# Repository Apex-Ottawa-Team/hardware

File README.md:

# Apex Hardware

## Overview

This repository contains the hardware design files for Ottawa Skybound's weather ballon for [Apex](https://apex.hackclub.com). The repository contains of multiple PCB modules designed in KiCad. The system includes a motherboard, wireless communication module, and various sensor interfaces.

## Boards

LoRa Module: Wireless communication module using LoRa technology. Designed by Adam Turaj

Motherboard: Main control board for the Apex system. Designed by Adam Turaj

Sensor Board: A board containing an IMU and temperature reader. Designed by Joshua Gallinger

Strain ADC: Analog-to-digital converter board for strain measurements. Designed by Adam Turaj

Archive/RF Module: Previous design iteration of the LoRa board. Designed by Adam Turaj

Gas Sensor: Collects data on TVOC concentrations in the air. Designed by Aryan Zafer

Ground RF: Board used to communicate and receive data from the weather balloon. Designed by Aryan Zafer

## Development Requirements

KiCad 9.0 or newer

## License

This project is licensed under the GNU GENERAL PUBLIC LICENSE. The license can be found [here](https://github.com/Apex-Ottawa-Team/hardware/blob/main/LICENSE).

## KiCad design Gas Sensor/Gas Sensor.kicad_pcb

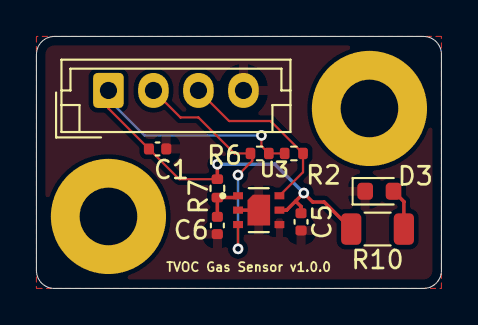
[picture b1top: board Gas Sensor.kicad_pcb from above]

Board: 2 copper layers, 22.5 x 14.0 mm, 10 parts (0 on the bottom side), 6 nets.

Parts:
C1: 10uF; C_0402_1005Metric
C5, C6: 0.1uF; C_0402_1005Metric
D3: LED; LED_0603_1608Metric
J1: Conn_Sensors; JST_EH_B4B-EH-A_1x04_P2.50mm_Vertical
R2, R6: 10k; R_0402_1005Metric
R7: 4.7; R_0402_1005Metric
R10: 220; R_1206_3216Metric
U3: SGP40-D-R4; XCDR_SGP40-D-R4

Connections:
+3.3V: C1.1, C5.1, J1.1 (VCC), R2.1, R6.2, R7.2, R10.1, U3.5 (VDDH)
GND: C1.2, C5.2, C6.2, D3.1 (K), J1.4 (GND), U3.2 (VSS), U3.4 (N/A), U3.7 (EXP)
unnamed: D3.2 (A), R10.2
unnamed: C6.1, R7.1, U3.1 (VDD)
SCL: J1.3 (SNS_SCL), R2.2, U3.6 (SCL)
SDA: J1.2 (SNS_SDA), R6.1, U3.3 (SDA)

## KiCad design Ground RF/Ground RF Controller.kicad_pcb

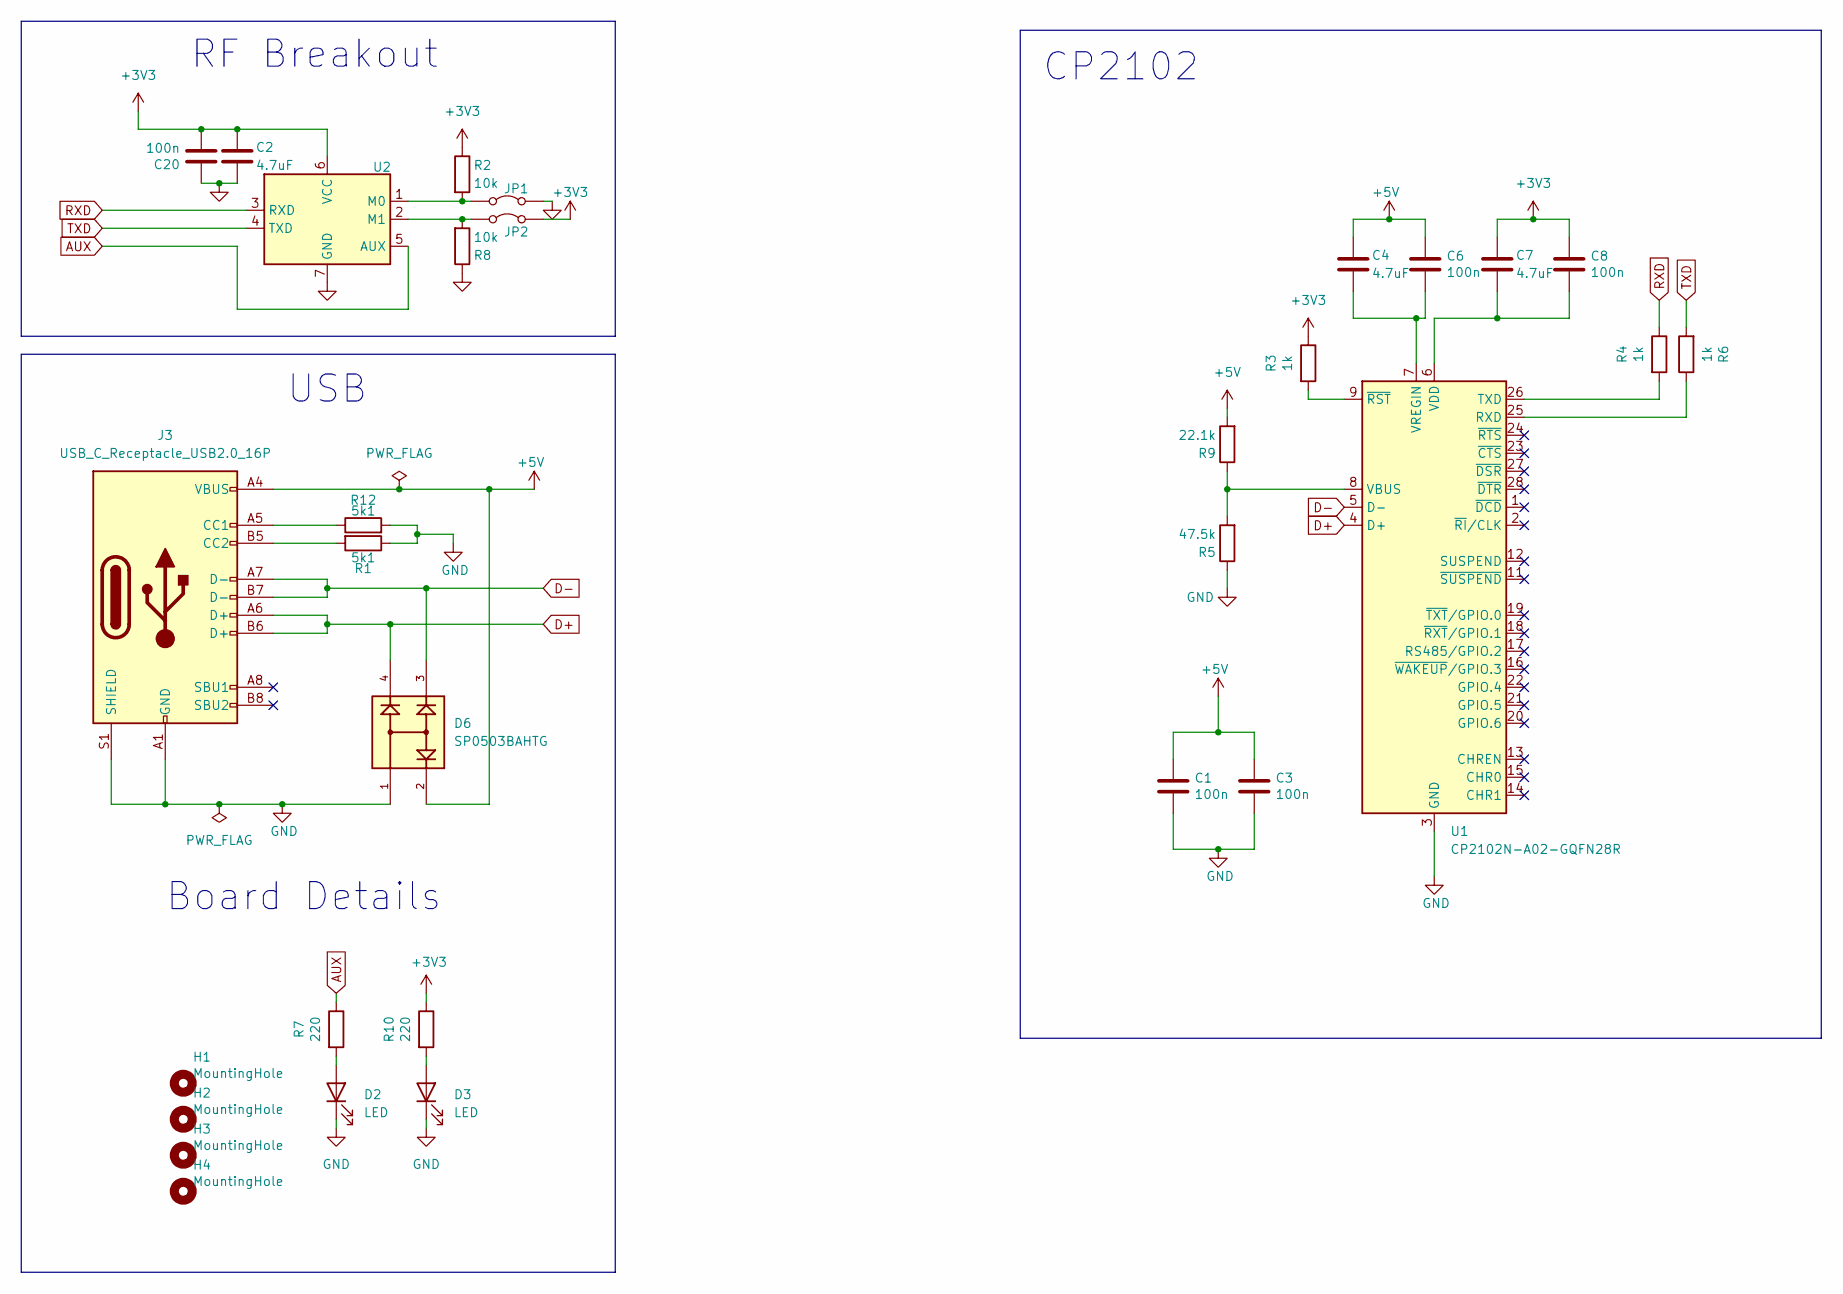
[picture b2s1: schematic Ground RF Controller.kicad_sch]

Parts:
C1, C3, C6, C8, C20: 100n; C_0402_1005Metric; MPN GRM152R61A104KE19D
C2, C4, C7: 4.7uF; C_0402_1005Metric; MPN GRM155R60J475ME47D
D2, D3: LED; LED_0603_1608Metric; MPN RC0603FR-075K1L
D6: SP0503BAHTG; SOT143; PARTREV N/A
H1, H2, H3, H4: MountingHole; MountingHole_2.7mm_M2.5
J3: USB_C_Receptacle_USB2.0_16P; USB_C_Receptacle_GCT_USB4105-xx-A_16P_TopMnt_Horizontal; MPN USB4105-GF-A-120
JP1, JP2: Jumper_2_Bridged; SolderJumper-2_P1.3mm_Open_RoundedPad1.0x1.5mm
R1, R12: 5k1; R_0603_1608Metric; MPN RC0603FR-075K1L
R2, R8: 10k; R_0402_1005Metric; MPN RC0402JR-0710KL
R3, R4, R6: 1k; R_0805_2012Metric; MPN RC0805JR-071KL
R5: 47.5k; R_0402_1005Metric; MPN CRCW040247K5FKEDC
R7, R10: 220; R_1206_3216Metric; MPN RC1206JR-10220RL
R9: 22.1k; R_0402_1005Metric; MPN CRCW040222K1FKEDC
U1: CP2102N-A02-GQFN28R; QFN-28-1EP_5x5mm_P0.5mm_EP3.35x3.35mm; MPN CP2102N-A02-GQFN28R
U2: EBYTE-E220-900T22D

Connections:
+3V3: C2.1, C7.1, C8.1, C20.2, JP2.2 (B), R2.1, R3.1, R10.1, U2.6 (VCC)
+5V: C1.1, C3.1, C4.1, C6.1, D6.2, J3.A4 (VBUS), J3.A9 (VBUS), J3.B4 (VBUS), J3.B9 (VBUS), R9.2
AUX: R7.1, U2.5 (AUX)
D+: D6.4, J3.A6 (D+), J3.B6 (D+), U1.4 (D+)
D-: D6.3, J3.A7 (D-), J3.B7 (D-), U1.5 (D-)
GND: C1.2, C2.2, C3.2, C20.1, D2.1 (K), D3.1 (K), D6.1, J3.A1 (GND), J3.A12 (GND), J3.B1 (GND), J3.B12 (GND), J3.S1 (SHIELD), JP1.2 (B), R1.1, R5.1, R8.1, R12.2, U1.3 (GND), U1.29 (GND), U2.7 (GND)
unnamed: D2.2 (A), R7.2
unnamed: D3.2 (A), R10.2
unnamed: J3.A5 (CC1), R12.1
unnamed: J3.B5 (CC2), R1.2
unnamed: JP1.1 (A), R2.2, U2.1 (M0)
unnamed: JP2.1 (A), R8.2, U2.2 (M1)
unnamed: R6.1, U1.25 (RXD)
unnamed: R4.2, U1.26 (TXD)
unnamed: R5.2, R9.1, U1.8 (VBUS)
unnamed: C7.2, C8.2, U1.6 (VDD)
unnamed: C4.2, C6.2, U1.7 (VREGIN)
unnamed: R3.2, U1.9 (~RST)
RXD: R4.1, U2.3 (RXD)
TXD: R6.2, U2.4 (TXD)

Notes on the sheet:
USB
CP2102
RF Breakout
Board Details

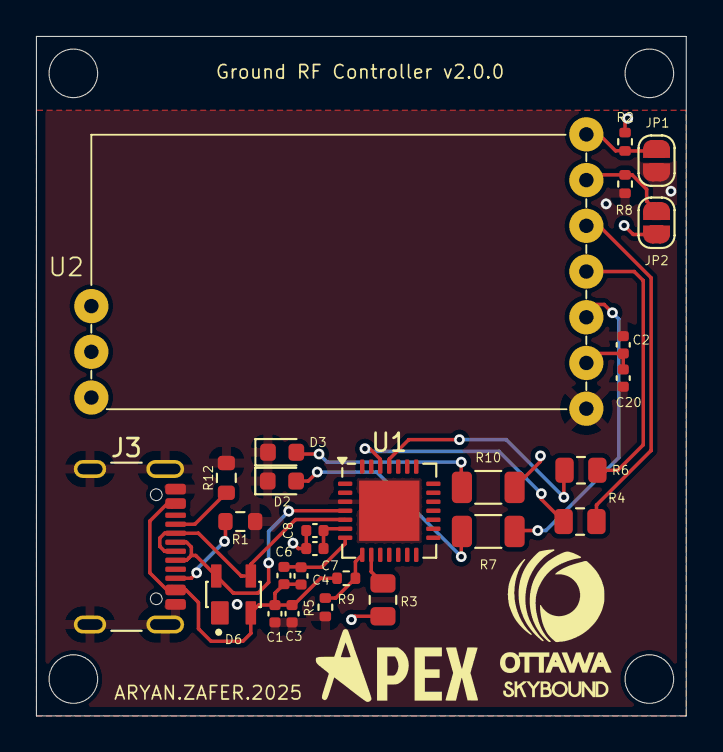
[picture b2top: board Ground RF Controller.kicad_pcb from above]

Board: 4 copper layers, 36.1 x 37.8 mm, 31 parts (0 on the bottom side), 20 nets.

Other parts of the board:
H3#2, H3#3, H3#4: MountingHole; MountingHole_2.7mm_M2.5

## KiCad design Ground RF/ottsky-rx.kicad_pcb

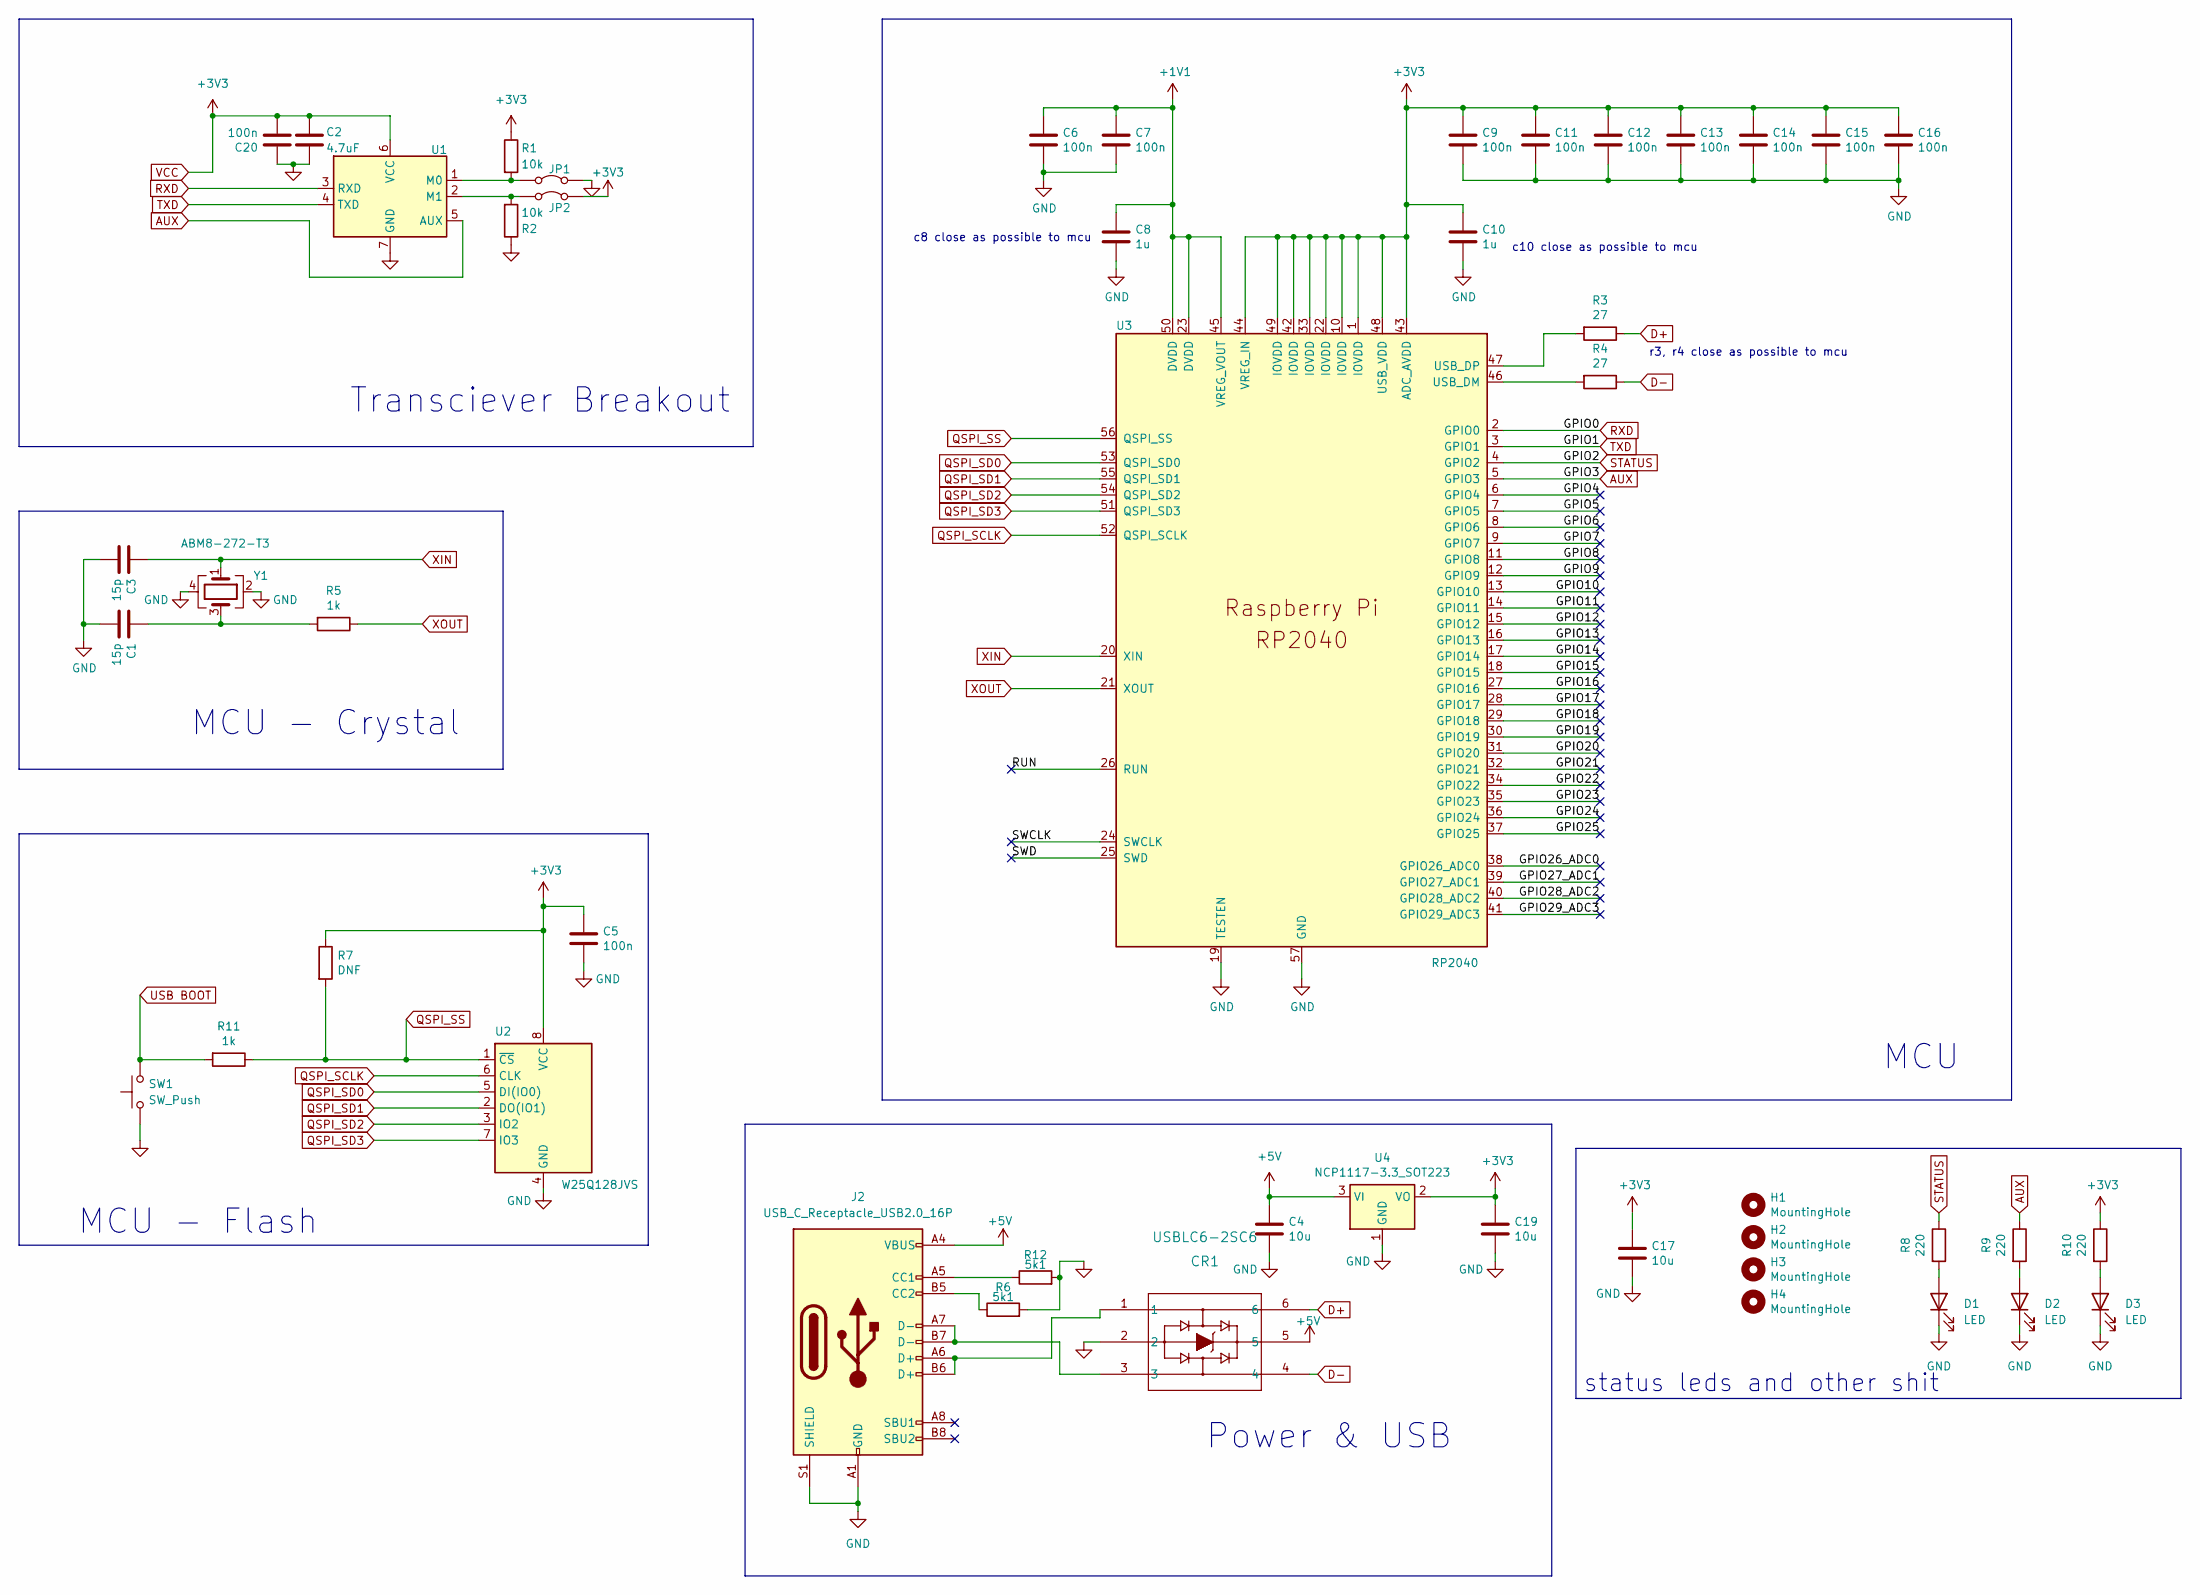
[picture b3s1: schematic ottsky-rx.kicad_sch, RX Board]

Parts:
C1, C3: 15p; C_0402_1005Metric; MPN GCQ1555C1H150JB01D
C2: 4.7uF; C_0402_1005Metric; MPN GRM155R60J475ME47D
C4, C17, C19: 10u; C_1210_3225Metric; MPN GMC32X5R106K50NT
C5, C6, C7, C9, C11, C12, C13, C14, C15, C16, C20: 100n; C_0402_1005Metric; MPN GRM152R61A104KE19D
C8: 1u; C_0402_1005Metric; MPN GRM152R60J105ME15D
C10: 1u; C_1206_3216Metric; MPN GRM31CR71E105KA01L
CR1: USBLC6-2SC6; SOT23-6L_STM; MPN USBLC6-2SC6
D1, D2, D3: LED; LED_0603_1608Metric; MPN RC0603FR-075K1L
H1, H2, H3, H4: MountingHole; MountingHole_2.7mm_M2.5
J2: USB_C_Receptacle_USB2.0_16P; USB_C_Receptacle_GCT_USB4105-xx-A_16P_TopMnt_Horizontal; MPN USB4105-GF-A-120
JP1, JP2: Jumper_2_Bridged; SolderJumper-2_P1.3mm_Open_RoundedPad1.0x1.5mm
R1, R2: 10k; R_0402_1005Metric; MPN RC0402JR-0710KL
R3, R4: 27; R_0402_1005Metric; MPN RC0402FR-7W27RL
R5, R11: 1k; R_0805_2012Metric; MPN RC0805JR-071KL
R6, R12: 5k1; R_0603_1608Metric; MPN RC0603FR-075K1L
R7: DNF; R_1206_3216Metric; MPN RC1206FR-130RL
R8, R9, R10: 220; R_1206_3216Metric; MPN RC1206JR-10220RL
SW1: SW_Push; SW_SPST_B3U-1000P; MPN B3U-1000P
U1: EBYTE-E220-900T22D
U2: W25Q128JVS; SOIC-8_5.23x5.23mm_P1.27mm; MPN W25Q128JVSIM TR
U3: RP2040; RP2040-QFN-56; MPN SC0914(13)
U4: NCP1117-3.3_SOT223; SOT-223-3_TabPin2; MPN NCP1117LPST33T3G
Y1: ABM8-272-T3; Crystal_SMD_3225-4Pin_3.2x2.5mm; MPN ABM8-272-T3

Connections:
+1V1: C6.1, C7.1, C8.1, U3.23 (DVDD), U3.45 (VREG_VOUT), U3.50 (DVDD)
+5V: C4.1, CR1.5, J2.A4 (VBUS), J2.A9 (VBUS), J2.B4 (VBUS), J2.B9 (VBUS), U4.3 (VI)
/GPIO4: U3.6 (GPIO4)
/GPIO5: U3.7 (GPIO5)
/GPIO6: U3.8 (GPIO6)
/GPIO7: U3.9 (GPIO7)
/GPIO8: U3.11 (GPIO8)
/GPIO9: U3.12 (GPIO9)
/GPIO10: U3.13 (GPIO10)
/GPIO11: U3.14 (GPIO11)
/GPIO12: U3.15 (GPIO12)
/GPIO13: U3.16 (GPIO13)
/GPIO14: U3.17 (GPIO14)
/GPIO15: U3.18 (GPIO15)
/GPIO16: U3.27 (GPIO16)
/GPIO17: U3.28 (GPIO17)
/GPIO18: U3.29 (GPIO18)
/GPIO19: U3.30 (GPIO19)
/GPIO20: U3.31 (GPIO20)
/GPIO21: U3.32 (GPIO21)
/GPIO22: U3.34 (GPIO22)
/GPIO23: U3.35 (GPIO23)
/GPIO24: U3.36 (GPIO24)
/GPIO25: U3.37 (GPIO25)
/GPIO26_ADC0: U3.38 (GPIO26_ADC0)
/GPIO27_ADC1: U3.39 (GPIO27_ADC1)
/GPIO28_ADC2: U3.40 (GPIO28_ADC2)
/GPIO29_ADC3: U3.41 (GPIO29_ADC3)
/RUN: U3.26 (RUN)
/SWCLK: U3.24 (SWCLK)
/SWD: U3.25 (SWD)
AUX: R9.1, U1.5 (AUX), U3.5 (GPIO3)
D+: CR1.6, R3.1
D-: CR1.4, R4.1
GND: C1.2, C2.2, C3.2, C4.2, C5.2, C6.2, C7.2, C8.2, C9.2, C10.2, C11.2, C12.2, C13.2, C14.2, C15.2, C16.2, C17.2, C19.2, C20.1, CR1.2, D1.1 (K), D2.1 (K), D3.1 (K), J2.A1 (GND), J2.A12 (GND), J2.B1 (GND), J2.B12 (GND), J2.S1 (SHIELD), JP1.2 (B), R2.1, R6.2, R12.2, SW1.1, U1.7 (GND), U2.4 (GND), U3.19 (TESTEN), U3.57 (GND), U4.1 (GND), Y1.2, Y1.4
unnamed: C1.1, R5.2, Y1.3
unnamed: CR1.1, J2.A6 (D+), J2.B6 (D+)
unnamed: CR1.3, J2.A7 (D-), J2.B7 (D-)
unnamed: D1.2 (A), R8.2
unnamed: D2.2 (A), R9.2
unnamed: D3.2 (A), R10.2
unnamed: J2.A5 (CC1), R12.1
unnamed: J2.B5 (CC2), R6.1
unnamed: JP1.1 (A), R1.2, U1.1 (M0)
unnamed: JP2.1 (A), R2.2, U1.2 (M1)
unnamed: R4.2, U3.46 (USB_DM)
unnamed: R3.2, U3.47 (USB_DP)
QSPI_SCLK: U2.6 (CLK), U3.52 (QSPI_SCLK)
QSPI_SD0: U2.5 (DI(IO0)), U3.53 (QSPI_SD0)
QSPI_SD1: U2.2 (DO(IO1)), U3.55 (QSPI_SD1)
QSPI_SD2: U2.3 (IO2), U3.54 (QSPI_SD2)
QSPI_SD3: U2.7 (IO3), U3.51 (QSPI_SD3)
QSPI_SS: R7.2, R11.1, U2.1 (~CS), U3.56 (QSPI_SS)
RXD: U1.3 (RXD), U3.2 (GPIO0)
STATUS: R8.1, U3.4 (GPIO2)
TXD: U1.4 (TXD), U3.3 (GPIO1)
USB BOOT: R11.2, SW1.2
VCC: C2.1, C5.1, C9.1, C10.1, C11.1, C12.1, C13.1, C14.1, C15.1, C16.1, C17.1, C19.1, C20.2, JP2.2 (B), R1.1, R7.1, R10.1, U1.6 (VCC), U2.8 (VCC), U3.1 (IOVDD), U3.10 (IOVDD), U3.22 (IOVDD), U3.33 (IOVDD), U3.42 (IOVDD), U3.43 (ADC_AVDD), U3.44 (VREG_IN), U3.48 (USB_VDD), U3.49 (IOVDD), U4.2 (VO)
XIN: C3.1, U3.20 (XIN), Y1.1
XOUT: R5.1, U3.21 (XOUT)

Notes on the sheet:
MCU - Flash
MCU
MCU - Crystal
status leds and other shit
c8 close as possible to mcu
c10 close as possible to mcu
Power & USB
r3, r4 close as possible to mcu
Transciever Breakout

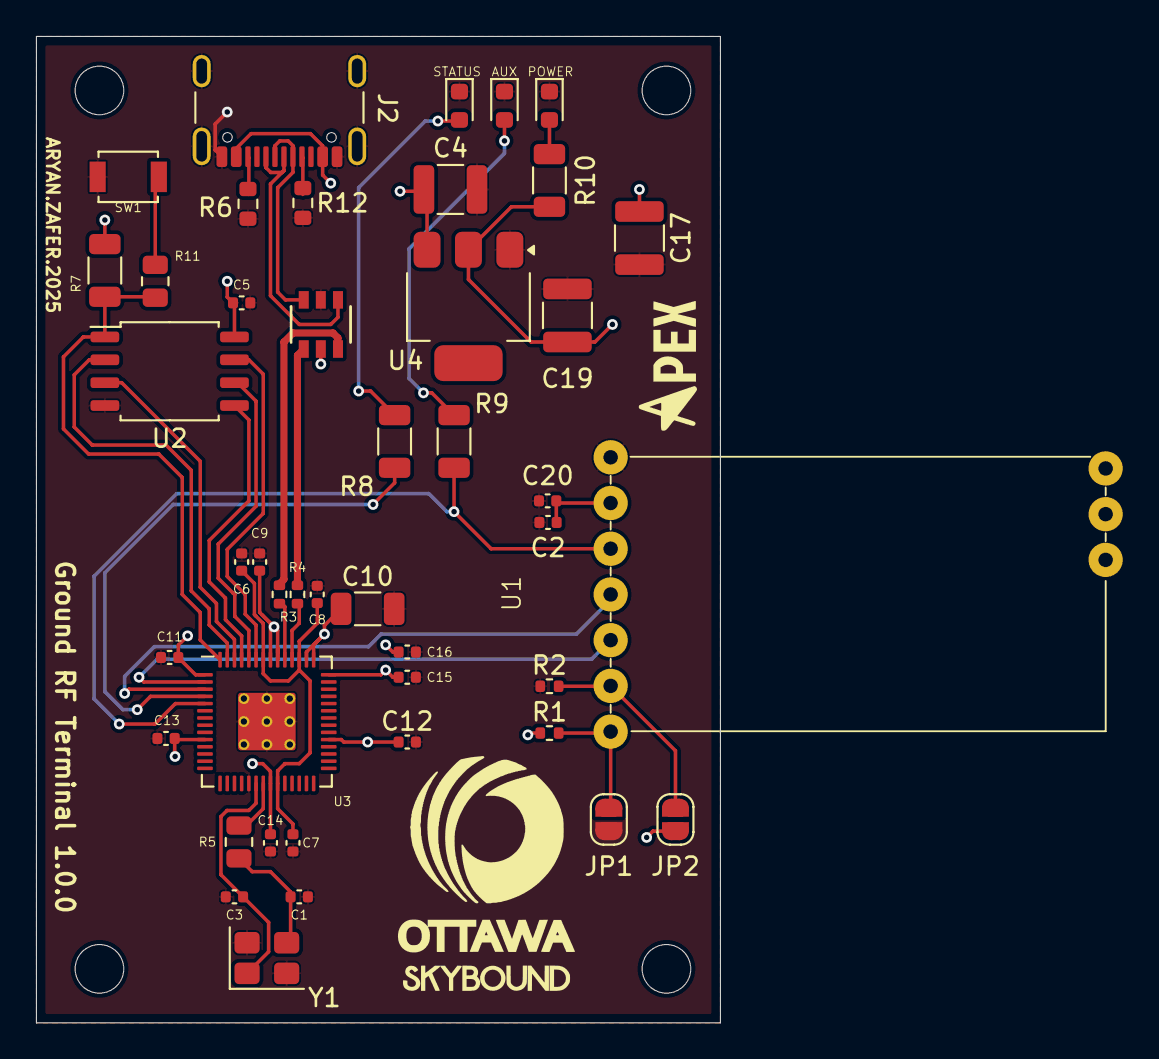
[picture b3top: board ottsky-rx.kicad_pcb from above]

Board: 4 copper layers, 38.0 x 54.8 mm, 48 parts (0 on the bottom side), 31 nets.

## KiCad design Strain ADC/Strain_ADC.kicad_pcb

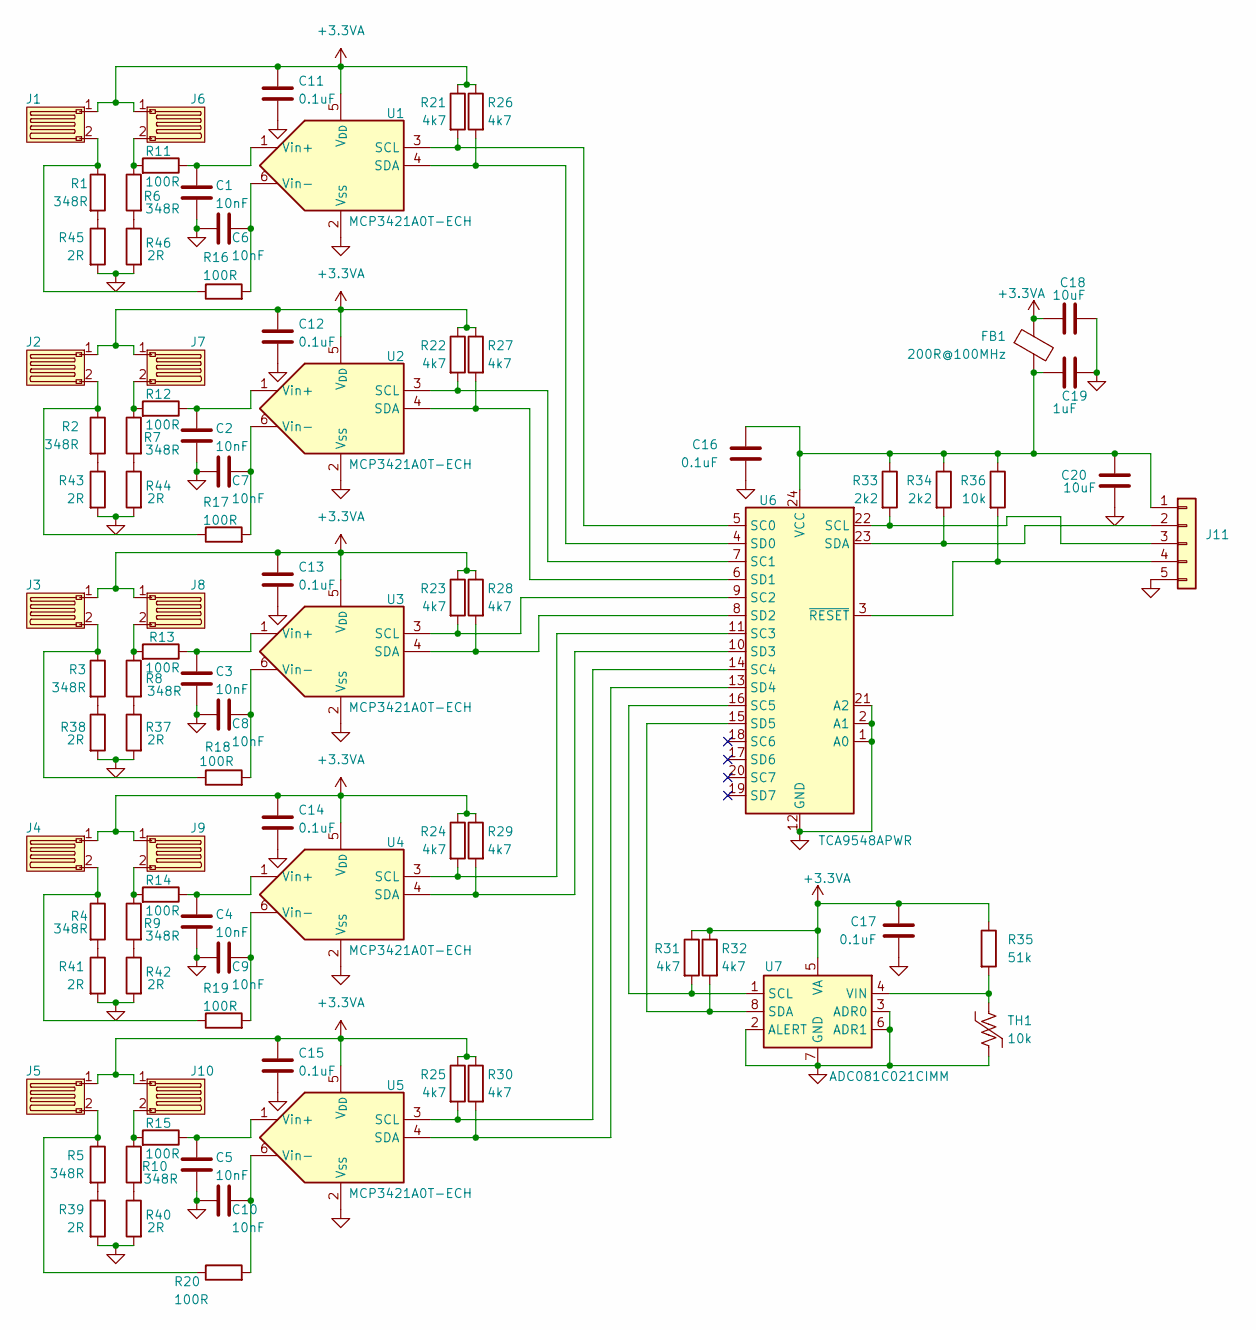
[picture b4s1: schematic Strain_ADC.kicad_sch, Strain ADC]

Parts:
C1, C2, C3, C4, C5, C6, C7, C8, C9, C10: 10nF; C_0402_1005Metric; Part Number GRM155R71C103KA01D
C11, C12, C13, C14, C15, C16, C17: 0.1uF; C_0402_1005Metric; Part Number CL05B104KP5NNNC
C18, C20: 10uF; C_0402_1005Metric; Part Number CL05A106MQ5NUNC
C19: 1uF; C_0402_1005Metric; Part Number GRM155R70J105KA12D
FB1: 200R@100MHz; L_0805_2012Metric; Part Number BLM21PG221SN1
J1, J2, J3, J4, J5, J6, J7, J8, J9, J10: R_0805_2012Metric
J11: Conn_01x05; JST_XH_B5B-XH-A_1x05_P2.50mm_Vertical; Part Number B5B-XH-A
R1, R2, R3, R4, R5, R6, R7, R8, R9, R10: 348R; R_0402_1005Metric; Part Number ERA-2AEB3480X
R11, R12, R13, R14, R15, R16, R17, R18, R19, R20: 100R; R_0402_1005Metric; Part Number CRCW0402100RFKEDC
R21, R22, R23, R24, R25, R26, R27, R28, R29, R30, R31, R32: 4k7; R_0402_1005Metric; Part Number RC0402FR-074K7L
R33, R34: 2k2; R_0402_1005Metric; Part Number RC0402FR-072K2L
R35: 51k; R_0402_1005Metric; Part Number ERJ-2RKF5102X
R36: 10k; R_0402_1005Metric; Part Number RC0402JR-0710KL
R37, R38, R39, R40, R41, R42, R43, R44, R45, R46: 2R; R_0603_1608Metric; Part Number RT0603BRE072RL
TH1: 10k; R_Axial_DIN0204_L3.6mm_D1.6mm_P2.54mm_Vertical; Part Number MF52A2103J3470
U1, U2, U3, U4, U5: MCP3421A0T-ECH; SOT-23-6; Part Number MCP3421A0T-E/CH
U6: TCA9548APWR; TSSOP-24_4.4x7.8mm_P0.65mm; Part Number TCA9548APWR
U7: ADC081C021CIMM; MSOP-8_3x3mm_P0.65mm; Part Number ADC081C021CIMKX/NOPB

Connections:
+3.3VA: C11.1, C12.1, C13.1, C14.1, C15.1, C17.1, C18.1, FB1.1, J1.1, J2.1, J3.1, J4.1, J5.1, J6.1, J7.1, J8.1, J9.1, J10.1, R21.1, R22.1, R23.1, R24.1, R25.1, R26.1, R27.1, R28.1, R29.1, R30.1, R31.1, R32.1, R35.1, U1.5 (V_{DD}), U2.5 (V_{DD}), U3.5 (V_{DD}), U4.5 (V_{DD}), U5.5 (V_{DD}), U7.5 (VA)
GND: C1.2, C2.2, C3.2, C4.2, C5.2, C6.2, C7.2, C8.2, C9.2, C10.2, C11.2, C12.2, C13.2, C14.2, C15.2, C16.2, C17.2, C18.2, C19.2, C20.1, J11.5, R37.2, R38.2, R39.2, R40.2, R41.2, R42.2, R43.2, R44.2, R45.2, R46.2, TH1.2, U1.2 (V_{SS}), U2.2 (V_{SS}), U3.2 (V_{SS}), U4.2 (V_{SS}), U5.2 (V_{SS}), U6.1 (A0), U6.2 (A1), U6.12 (GND), U6.21 (A2), U7.2 (ALERT), U7.3 (ADR0), U7.6 (ADR1), U7.7 (GND)
unnamed: J1.2, R1.1, R16.1
unnamed: J2.2, R2.1, R17.1
unnamed: J3.2, R3.1, R18.1
unnamed: J4.2, R4.1, R19.1
unnamed: J5.2, R5.1, R20.1
unnamed: J6.2, R6.1, R11.2
unnamed: J7.2, R7.1, R12.2
unnamed: J8.2, R8.1, R13.2
unnamed: J9.2, R9.1, R14.2
unnamed: J10.2, R10.1, R15.2
unnamed: C16.1, C19.1, C20.2, FB1.2, J11.1, R33.1, R34.1, R36.1, U6.24 (VCC)
unnamed: J11.2, R34.2, U6.23 (SDA)
unnamed: J11.3, R33.2, U6.22 (SCL)
unnamed: J11.4, R36.2, U6.3 (~RESET)
unnamed: R1.2, R45.1
unnamed: R2.2, R43.1
unnamed: R3.2, R38.1
unnamed: R4.2, R41.1
unnamed: R10.2, R40.1
unnamed: R8.2, R37.1
unnamed: R5.2, R39.1
unnamed: R9.2, R42.1
unnamed: R7.2, R44.1
unnamed: R6.2, R46.1
unnamed: R21.2, U1.3 (SCL), U6.5 (SC0)
unnamed: R26.2, U1.4 (SDA), U6.4 (SD0)
unnamed: C1.1, R11.1, U1.1 (Vin+)
unnamed: C6.1, R16.2, U1.6 (Vin-)
unnamed: R22.2, U2.3 (SCL), U6.7 (SC1)
unnamed: R27.2, U2.4 (SDA), U6.6 (SD1)
unnamed: C2.1, R12.1, U2.1 (Vin+)
unnamed: C7.1, R17.2, U2.6 (Vin-)
unnamed: R23.2, U3.3 (SCL), U6.9 (SC2)
unnamed: R28.2, U3.4 (SDA), U6.8 (SD2)
unnamed: C3.1, R13.1, U3.1 (Vin+)
unnamed: C8.1, R18.2, U3.6 (Vin-)
unnamed: R24.2, U4.3 (SCL), U6.11 (SC3)
unnamed: R29.2, U4.4 (SDA), U6.10 (SD3)
unnamed: C4.1, R14.1, U4.1 (Vin+)
unnamed: C9.1, R19.2, U4.6 (Vin-)
unnamed: R25.2, U5.3 (SCL), U6.14 (SC4)
unnamed: R30.2, U5.4 (SDA), U6.13 (SD4)
unnamed: C5.1, R15.1, U5.1 (Vin+)
unnamed: C10.1, R20.2, U5.6 (Vin-)
unnamed: R31.2, U6.16 (SC5), U7.1 (SCL)
unnamed: R32.2, U6.15 (SD5), U7.8 (SDA)
unnamed: R35.2, TH1.1, U7.4 (VIN)

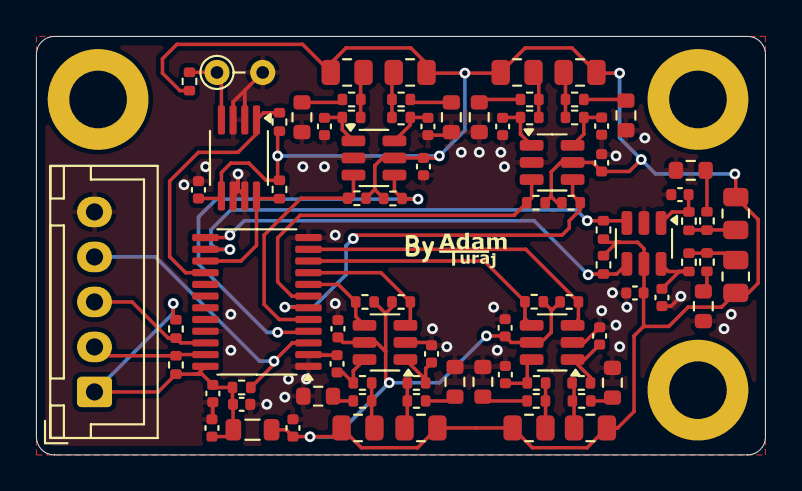
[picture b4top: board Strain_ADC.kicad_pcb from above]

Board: 2 copper layers, 40.5 x 23.2 mm, 86 parts (0 on the bottom side), 49 nets.

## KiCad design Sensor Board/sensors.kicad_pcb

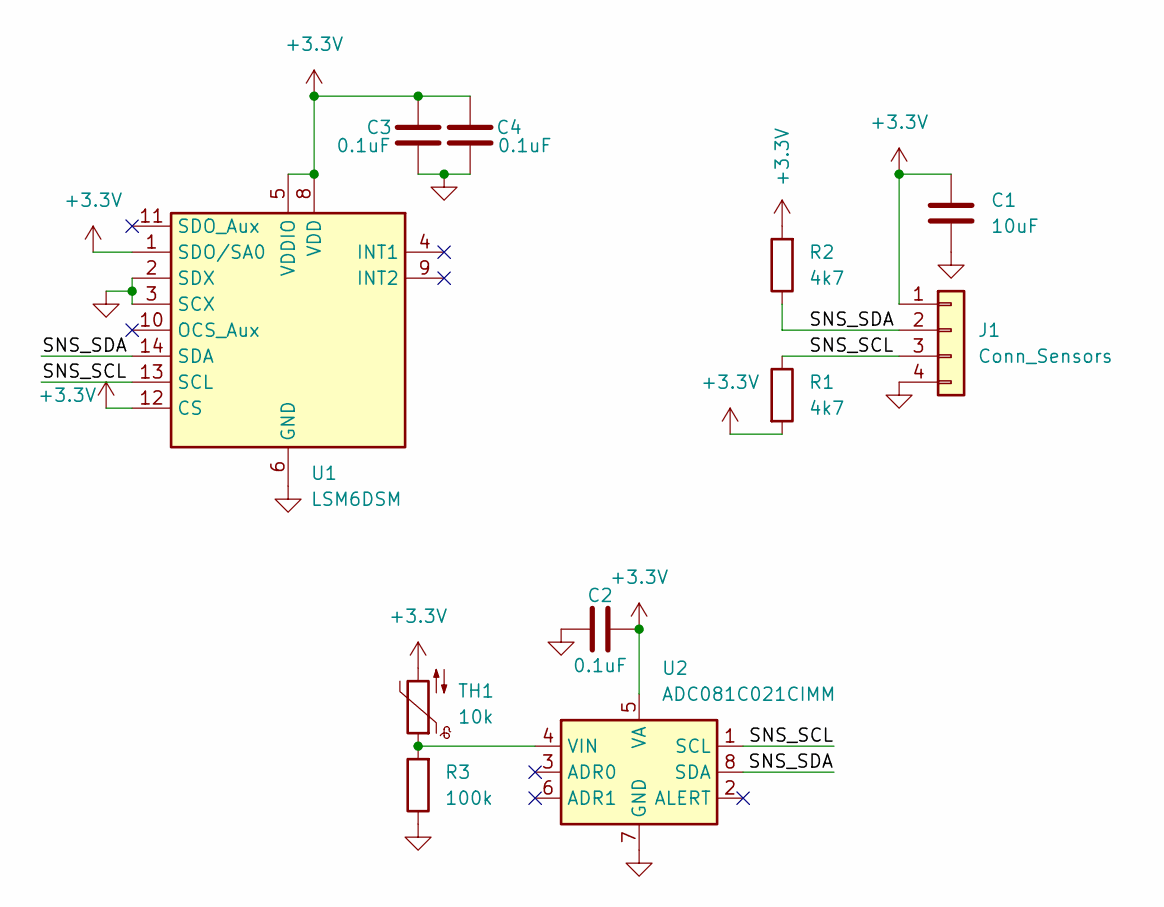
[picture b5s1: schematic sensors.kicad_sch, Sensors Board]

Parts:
C1: 10uF; C_0402_1005Metric; MPN 0402W106M6R3HI
C2, C3, C4: 0.1uF; C_0402_1005Metric; MPN 0402B104K160HI
J1: Conn_Sensors; JST_EH_B4B-EH-A_1x04_P2.50mm_Vertical; MPN B4B-XH-A
R1, R2: 4k7; R_0402_1005Metric; MPN RC0402JR-074K7L
R3: 100k; R_0402_1005Metric; MPN RC0402JR-07100KL
TH1: 10k; R_0402_1005Metric; MPN NCU15XH103F6SRC
U1: LSM6DSM; LGA-14_3x2.5mm_P0.5mm_LayoutBorder3x4y; MPN LSM6DSVTR
U2: ADC081C021CIMM; MSOP-8_3x3mm_P0.65mm; MPN ADC081C021CIMM/NOPB

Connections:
+3.3V: C1.1, C2.2, C3.1, C4.1, J1.1 (VCC), R1.2, R2.2, TH1.2, U1.1 (SDO/SA0), U1.5 (VDDIO), U1.8 (VDD), U1.12 (CS), U2.5 (VA)
/SNS_SCL: J1.3 (SNS_SCL), R1.1, U1.13 (SCL), U2.1 (SCL)
/SNS_SDA: J1.2 (SNS_SDA), R2.1, U1.14 (SDA), U2.8 (SDA)
GND: C1.2, C2.1, C3.2, C4.2, J1.4 (GND), R3.1, U1.2 (SDX), U1.3 (SCX), U1.6 (GND), U1.7 (GND), U2.7 (GND)
unnamed: R3.2, TH1.1, U2.4 (VIN)

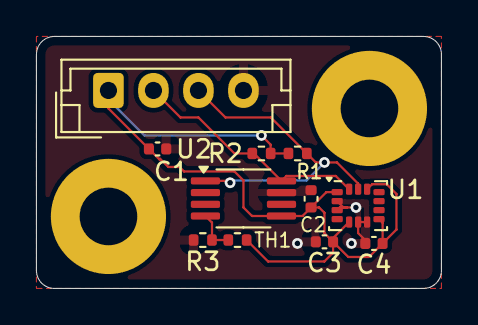
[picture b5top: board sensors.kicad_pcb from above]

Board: 2 copper layers, 22.5 x 14.0 mm, 11 parts (0 on the bottom side), 5 nets.

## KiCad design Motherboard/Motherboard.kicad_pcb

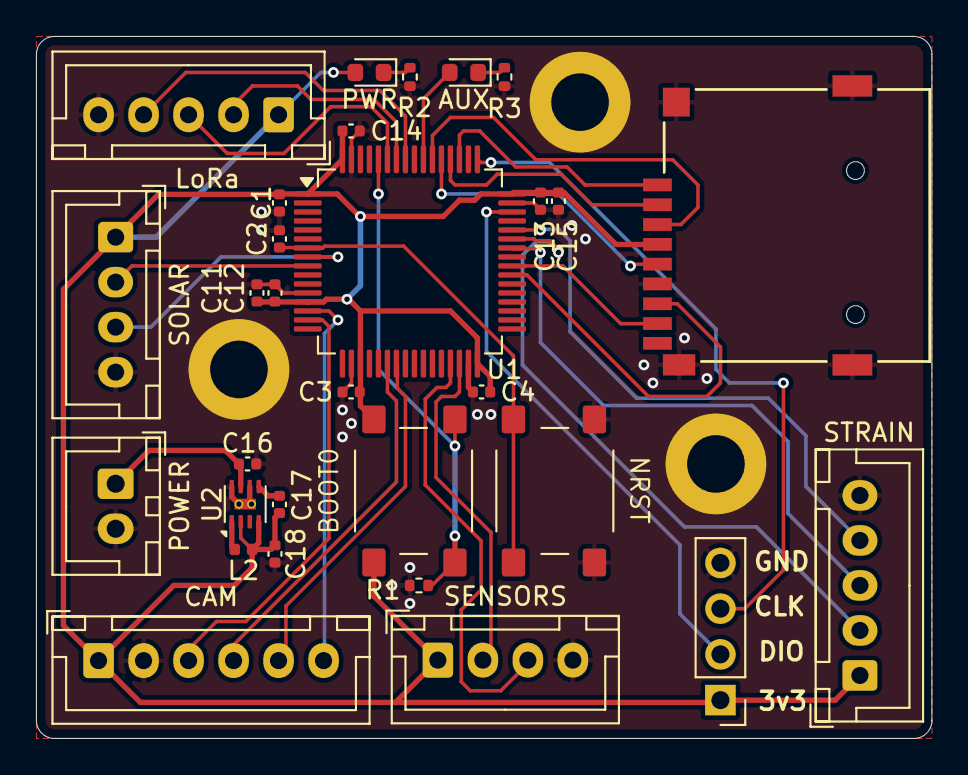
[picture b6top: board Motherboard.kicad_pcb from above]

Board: 2 copper layers, 49.8 x 39.0 mm, 30 parts (0 on the bottom side), 32 nets.

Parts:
AUX: GREEN; LED_0603_1608Metric
BOOT0: BOOT0; SW_Push_SMD_6mm
C1, C2, C3, C4, C11, C13, C14: 0.1uF; C_0402_1005Metric
C12: 1uF; C_0402_1005Metric
C15: 10uF; C_0402_1005Metric
C16, C18: 4.7uF; C_0402_1005Metric
C17: 560pF; C_0402_1005Metric
CAM: Conn_Cam; JST_XH_B6B-XH-A_1x06_P2.50mm_Vertical
J3: Micro_SD_Card; CONN9_MSD-1_CUD
J4: Conn_SW; PinHeader_1x04_P2.54mm_Vertical
L2: 1uH; L_0402_1005Metric
LoRa: Conn_RF; JST_XH_B5B-XH-A_1x05_P2.50mm_Vertical
NRST: NRST; SW_Push_SMD_6mm
POWER: Conn_Power; JST_XH_B2B-XH-A_1x02_P2.50mm_Vertical
PWR: RED; LED_0603_1608Metric
R1: 10k; R_0402_1005Metric
R2, R3: 560R; R_0402_1005Metric
SENSORS: Conn_Sensors; JST_XH_B4B-XH-A_1x04_P2.50mm_Vertical
SOLAR: Conn_Solar; JST_XH_B4B-XH-A_1x04_P2.50mm_Vertical
STRAIN: Conn_Strain; JST_XH_B5B-XH-A_1x05_P2.50mm_Vertical
U1: STM32L431RCTx; LQFP-64_10x10mm_P0.5mm
U2: MIC23050-SYML; Micrel_MLF-8-1EP_2x2mm_P0.5mm_EP0.6x1.2mm_ThermalVias

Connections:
+3V3: BOOT0.1, C1.1, C3.1, C4.1, C11.1, C12.1, C13.1, C14.1, C15.1, C17.1, C18.1, CAM.1, J3.4 (VDD), J4.1, L2.1, LoRa.1, PWR.2 (A), SENSORS.1, SOLAR.1, STRAIN.1, U1.1 (VBAT), U1.13 (VDDA), U1.19 (VDD), U1.32 (VDD), U1.48 (VDD), U1.64 (VDD), U2.2 (EN), U2.4 (SNS)
/CAM_CS: CAM.6, U1.14 (PA0)
/CAM_MISO: CAM.4, U1.22 (PA6)
/CAM_MOSI: CAM.5, U1.23 (PA7)
/CAM_SCK: CAM.3, U1.15 (PA1)
/LoRa_INT: LoRa.4, U1.57 (PB5)
/LoRa_RX: LoRa.2, U1.58 (PB6)
/LoRa_TX: LoRa.3, U1.59 (PB7)
/SD_CK: J3.5 (CLK), U1.53 (PC12)
/SD_CMD: J3.3 (CMD), U1.54 (PD2)
/SD_D0: J3.7 (DAT0), U1.39 (PC8)
/SD_D1: J3.8 (DAT1), U1.40 (PC9)
/SD_D2: J3.1 (DAT2), U1.51 (PC10)
/SD_D3: J3.2 (DAT3/CD), U1.52 (PC11)
/SWCLK: J4.3, U1.49 (PA14)
/SWDIO: J4.2, U1.46 (PA13)
/Sensors_SCL: SENSORS.3, U1.29 (PB10)
/Sensors_SDA: SENSORS.2, U1.30 (PB11)
/Solar_SCL: SOLAR.3, U1.8 (PC0)
/Solar_SDA: SOLAR.2, U1.9 (PC1)
/Strain_RST: STRAIN.4, U1.44 (PA11)
/Strain_SCL: STRAIN.3, U1.42 (PA9)
/Strain_SDA: STRAIN.2, U1.43 (PA10)
GND: C1.2, C2.1, C3.2, C4.2, C11.2, C12.2, C13.2, C14.2, C15.2, C16.2, C18.2, CAM.2, J3.6 (VSS), J3.9 (SHIELD), J4.4, LoRa.5, NRST.1, POWER.2, R1.2, R2.2, R3.2, SENSORS.4, SOLAR.4, STRAIN.5, U1.12 (VSSA), U1.18 (VSS), U1.31 (VSS), U1.47 (VSS), U1.63 (VSS), U2.6 (AGND), U2.8 (PGND), U2.9 (EP_GND)
unnamed: PWR.1 (K), R2.1
unnamed: AUX.2 (A), U1.55 (PB3)
unnamed: AUX.1 (K), R3.1
unnamed: C16.1, POWER.1, U2.7 (VIN)
unnamed: C2.2, NRST.2, U1.7 (NRST)
unnamed: BOOT0.2, R1.1, U1.60 (PH3)
unnamed: C17.2, U2.5 (CFF)
unnamed: L2.2, U2.1 (SW)

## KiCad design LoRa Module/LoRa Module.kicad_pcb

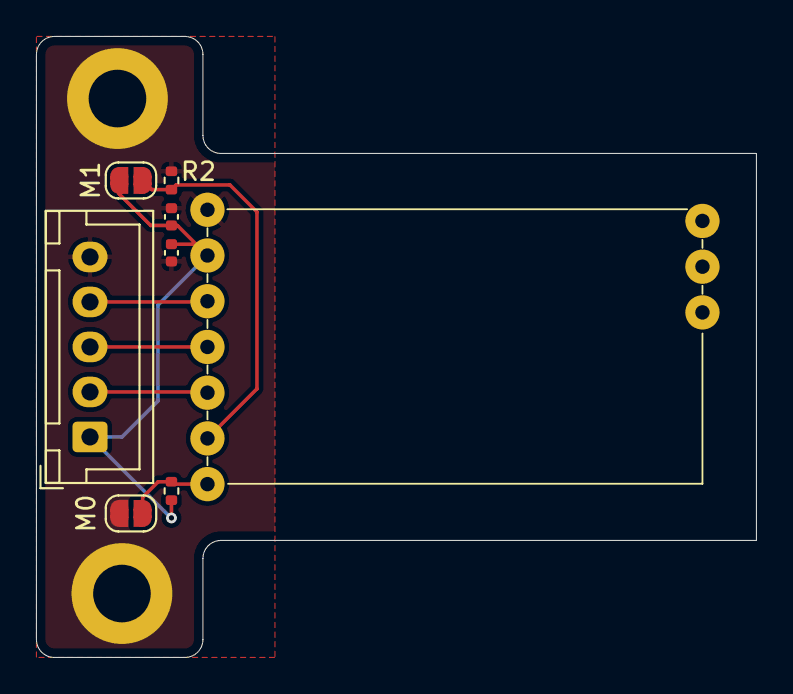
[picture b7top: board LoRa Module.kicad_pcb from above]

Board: 2 copper layers, 40.0 x 34.5 mm, 8 parts (0 on the bottom side), 7 nets.

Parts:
C1: 0.1uF; C_0402_1005Metric
C2: 4.7uF; C_0402_1005Metric
J1: Conn_MB; JST_XH_B5B-XH-A_1x05_P2.50mm_Vertical
M0, M1: Jumper_2_Bridged; SolderJumper-2_P1.3mm_Open_RoundedPad1.0x1.5mm
R1, R2: 10k; R_0402_1005Metric
U1: EBYTE-E220-900T22D

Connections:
+3V3: C1.1, C2.1, J1.1, M1.2 (B), R1.1, U1.6 (VCC)
GND: C1.2, C2.2, J1.5, M0.2 (B), R2.1, U1.7 (GND)
unnamed: J1.2, U1.3 (RXD)
unnamed: J1.3, U1.4 (TXD)
unnamed: J1.4, U1.5 (AUX)
unnamed: M0.1 (A), R1.2, U1.1 (M0)
unnamed: M1.1 (A), R2.2, U1.2 (M1)

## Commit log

2025-05-31 Hello World!
2025-06-01 add MPNs for sensor board components - rts4
2025-06-01 Add README and License. Rename folder, minor changes to PCB
2025-06-02 Add part numbers to remaining PCBs, change part numbers on sensor board, redo strain adc layout
2025-06-10 Final Ground RF
2025-06-10 Formal
2025-06-11 Starting v2.0.0 schematic
2025-06-11 v2.0.0 Ground RF finished
2025-06-11 PCB cleanup
2025-06-11 Ground RF BOM
2025-06-11 v1.0.0 TVOC Gas Sensor complete.
2025-06-11 Gas Sensor PCB cleanup
